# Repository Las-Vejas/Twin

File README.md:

# Twin
A macropad for both your computer and Home Assistant. Controls PC as an HID device, controls Home Assistant via ESPHome. 

I built this because I wanted a central place to control both my home/room, and my computer at the same time.
This device switches between the Home Assistant mode and PC mode with a click of a button and you receive all the feedback through the 25 leds on board.

This macropad contains:
- 14 underglow leds
- 11 switches (with leds underneath)
- RP2040
- ESP32-C6
- 1 rotary encoder

## Images

### Schematic

### PCB

## BOM

|Id |Footprint                                              |Designation                |LCSC     |Amount|Price    |Link                                                                                                                                                                                                                                                                                                                                                                                                                                                                                                                                                                                                                                                                 |
|---|-------------------------------------------------------|---------------------------|---------|------|---------|---------------------------------------------------------------------------------------------------------------------------------------------------------------------------------------------------------------------------------------------------------------------------------------------------------------------------------------------------------------------------------------------------------------------------------------------------------------------------------------------------------------------------------------------------------------------------------------------------------------------------------------------------------------------|
|1  |C_0402_1005Metric                                      |1uf                        |C14445   |100   |0.23 $US |https://www.lcsc.com/product-detail/C14445.html                                                                                                                                                                                                                                                                                                                                                                                                                                                                                                                                                                                                                      |
|2  |C_0402_1005Metric                                      |100nf                      |C60474   |100   |0.10 $US |https://www.lcsc.com/product-detail/C60474.html                                                                                                                                                                                                                                                                                                                                                                                                                                                                                                                                                                                                                      |
|3  |C_0402_1005Metric                                      |10uf                       |C315248  |20    |0.17 $US |https://www.lcsc.com/product-detail/C315248.html                                                                                                                                                                                                                                                                                                                                                                                                                                                                                                                                                                                                                     |
|4  |C_0402_1005Metric                                      |33pf                       |C107005  |100   |0.12 $US |https://www.lcsc.com/product-detail/C107005.html                                                                                                                                                                                                                                                                                                                                                                                                                                                                                                                                                                                                                     |
|7  |LED_WS2812B-2020_PLCC4_2.0x2.0mm                       |WS2812B-2020               |C965555  |40    |3.59 $US |https://www.lcsc.com/product-detail/C965555.html                                                                                                                                                                                                                                                                                                                                                                                                                                                                                                                                                                                                                     |
|8  |D_SOD-323_HandSoldering                                |D_Small                    |C191023  |50    |0.52 $US |https://www.lcsc.com/product-detail/C191023.html                                                                                                                                                                                                                                                                                                                                                                                                                                                                                                                                                                                                                     |
|9  |MX_SK6812MINI-E                                        |LED_SK6812MINI             |C5149201 |55    |4.13 $US |https://www.lcsc.com/product-detail/C5149201.html                                                                                                                                                                                                                                                                                                                                                                                                                                                                                                                                                                                                                    |
|10 |USB_C_Receptacle_GCT_USB4105-xx-A_16P_TopMnt_Horizontal|USB_C_Receptacle_USB2.0_16P|C2765186 |20    |1.23 $US |https://www.lcsc.com/product-detail/C2765186.html                                                                                                                                                                                                                                                                                                                                                                                                                                                                                                                                                                                                                    |
|12 |C_0402_1005Metric                                      |10k                        |C60490   |100   |0.08 $US |https://www.lcsc.com/product-detail/C60490.html                                                                                                                                                                                                                                                                                                                                                                                                                                                                                                                                                                                                                      |
|13 |C_0402_1005Metric                                      |5.1k                       |C105872  |100   |0.09 $US |https://www.lcsc.com/product-detail/C105872.html                                                                                                                                                                                                                                                                                                                                                                                                                                                                                                                                                                                                                     |
|14 |C_0402_1005Metric                                      |27                         |C138021  |100   |0.08 $US |https://www.lcsc.com/product-detail/C138021.html                                                                                                                                                                                                                                                                                                                                                                                                                                                                                                                                                                                                                     |
|15 |C_0402_1005Metric                                      |1k                         |C106235  |100   |0.08 $US |https://www.lcsc.com/product-detail/C106235.html                                                                                                                                                                                                                                                                                                                                                                                                                                                                                                                                                                                                                     |
|16 |C_0402_1005Metric                                      |47                         |C137973  |100   |0.09 $US |https://www.lcsc.com/product-detail/C137973.html                                                                                                                                                                                                                                                                                                                                                                                                                                                                                                                                                                                                                     |
|17 |SW_Push_SPST_NO_Alps_SKRK                              |SW_Push                    |C115357  |10    |1.31 $US |https://www.lcsc.com/product-detail/C115357.html                                                                                                                                                                                                                                                                                                                                                                                                                                                                                                                                                                                                                     |
|18 |RotaryEncoder_Alps_EC11E-Switch_Vertical_H20mm         |RotaryEncoder_Switch       |C470742  |5     |9.36 $US |https://www.lcsc.com/product-detail/C470742.html                                                                                                                                                                                                                                                                                                                                                                                                                                                                                                                                                                                                                     |
|19 |Choc_V1V2_1.00u                                        |Choc                       |         |20    |13.22 $US|https://fr.aliexpress.com/item/1005008651091078.html?spm=a2g0o.productlist.main.4.700d4fcbBPonj4&algo_pvid=be3ccfad-3712-46f3-9d73-c757c8aa3e61&algo_exp_id=be3ccfad-3712-46f3-9d73-c757c8aa3e61-3&pdp_ext_f=%7B%22order%22%3A%22447%22%2C%22eval%22%3A%221%22%2C%22fromPage%22%3A%22search%22%7D&pdp_npi=6%40dis%21EUR%216.61%215.24%21%21%2151.22%2140.63%21%40214100f417755480393871686e909e%2112000046099032296%21sea%21LU%212630435768%21X%211%210%21n_tag%3A-29919%3Bd%3Af72fadc9%3Bm03_new_user%3A-29895%3BpisId%3A5000000202142352&curPageLogUid=yKcuHdsHmziV&utparam-url=scene%3Asearch%7Cquery_from%3A%7Cx_object_id%3A1005008651091078%7C_p_origin_prod%3A|
|21 |SOT-23                                                 |MCP1700x-300xxTT           |C39051   |5     |1.88 $US |https://www.lcsc.com/product-detail/C39051.html                                                                                                                                                                                                                                                                                                                                                                                                                                                                                                                                                                                                                      |
|22 |ESP32-C6-MINI-1                                        |ESP32-C6-MINI-1            |C5736265 |5     |11.97 $US|https://www.lcsc.com/product-detail/C5736265.html                                                                                                                                                                                                                                                                                                                                                                                                                                                                                                                                                                                                                    |
|23 |QFN-56-1EP_7x7mm_P0.4mm_EP3.2x3.2mm                    |RP2040                     |C2040    |5     |4.74 $US |https://www.lcsc.com/product-detail/C2040.html                                                                                                                                                                                                                                                                                                                                                                                                                                                                                                                                                                                                                       |
|24 |Winbond_USON-8-1EP_3x2mm_P0.5mm_EP0.2x1.6mm            |W25Q16JVSS                 |C5258281 |10    |2.74 $US |https://www.lcsc.com/product-detail/C5258281.html                                                                                                                                                                                                                                                                                                                                                                                                                                                                                                                                                                                                                    |
|25 |Crystal_SMD_3225-4Pin_3.2x2.5mm                        |12MHz                      |C20625731|5     |1.45 $US |https://www.lcsc.com/product-detail/C20625731.html                                                                                                                                                                                                                                                                                                                                                                                                                                                                                                                                                                                                                   |
|   |PCB                                                    |                           |         |5     |7.00 $US |jlcpcb.com                                                                                                                                                                                                                                                                                                                                                                                                                                                                                                                                                                                                                                                           |
|   |Stencil                                                |                           |         |1     |3.05 $US |jlcpcb.com                                                                                                                                                                                                                                                                                                                                                                                                                                                                                                                                                                                                                                                           |
|   |PCB Shipping                                           |                           |         |1     |15.00 $US|jlcpcb.com                                                                                                                                                                                                                                                                                                                                                                                                                                                                                                                                                                                                                                                           |
|   |                                                       |                           |         |      |81.90 $US|                                                                                                                                                                                                                                                                                                                                                                                                                                                                                                                                                                                                                                                                     |

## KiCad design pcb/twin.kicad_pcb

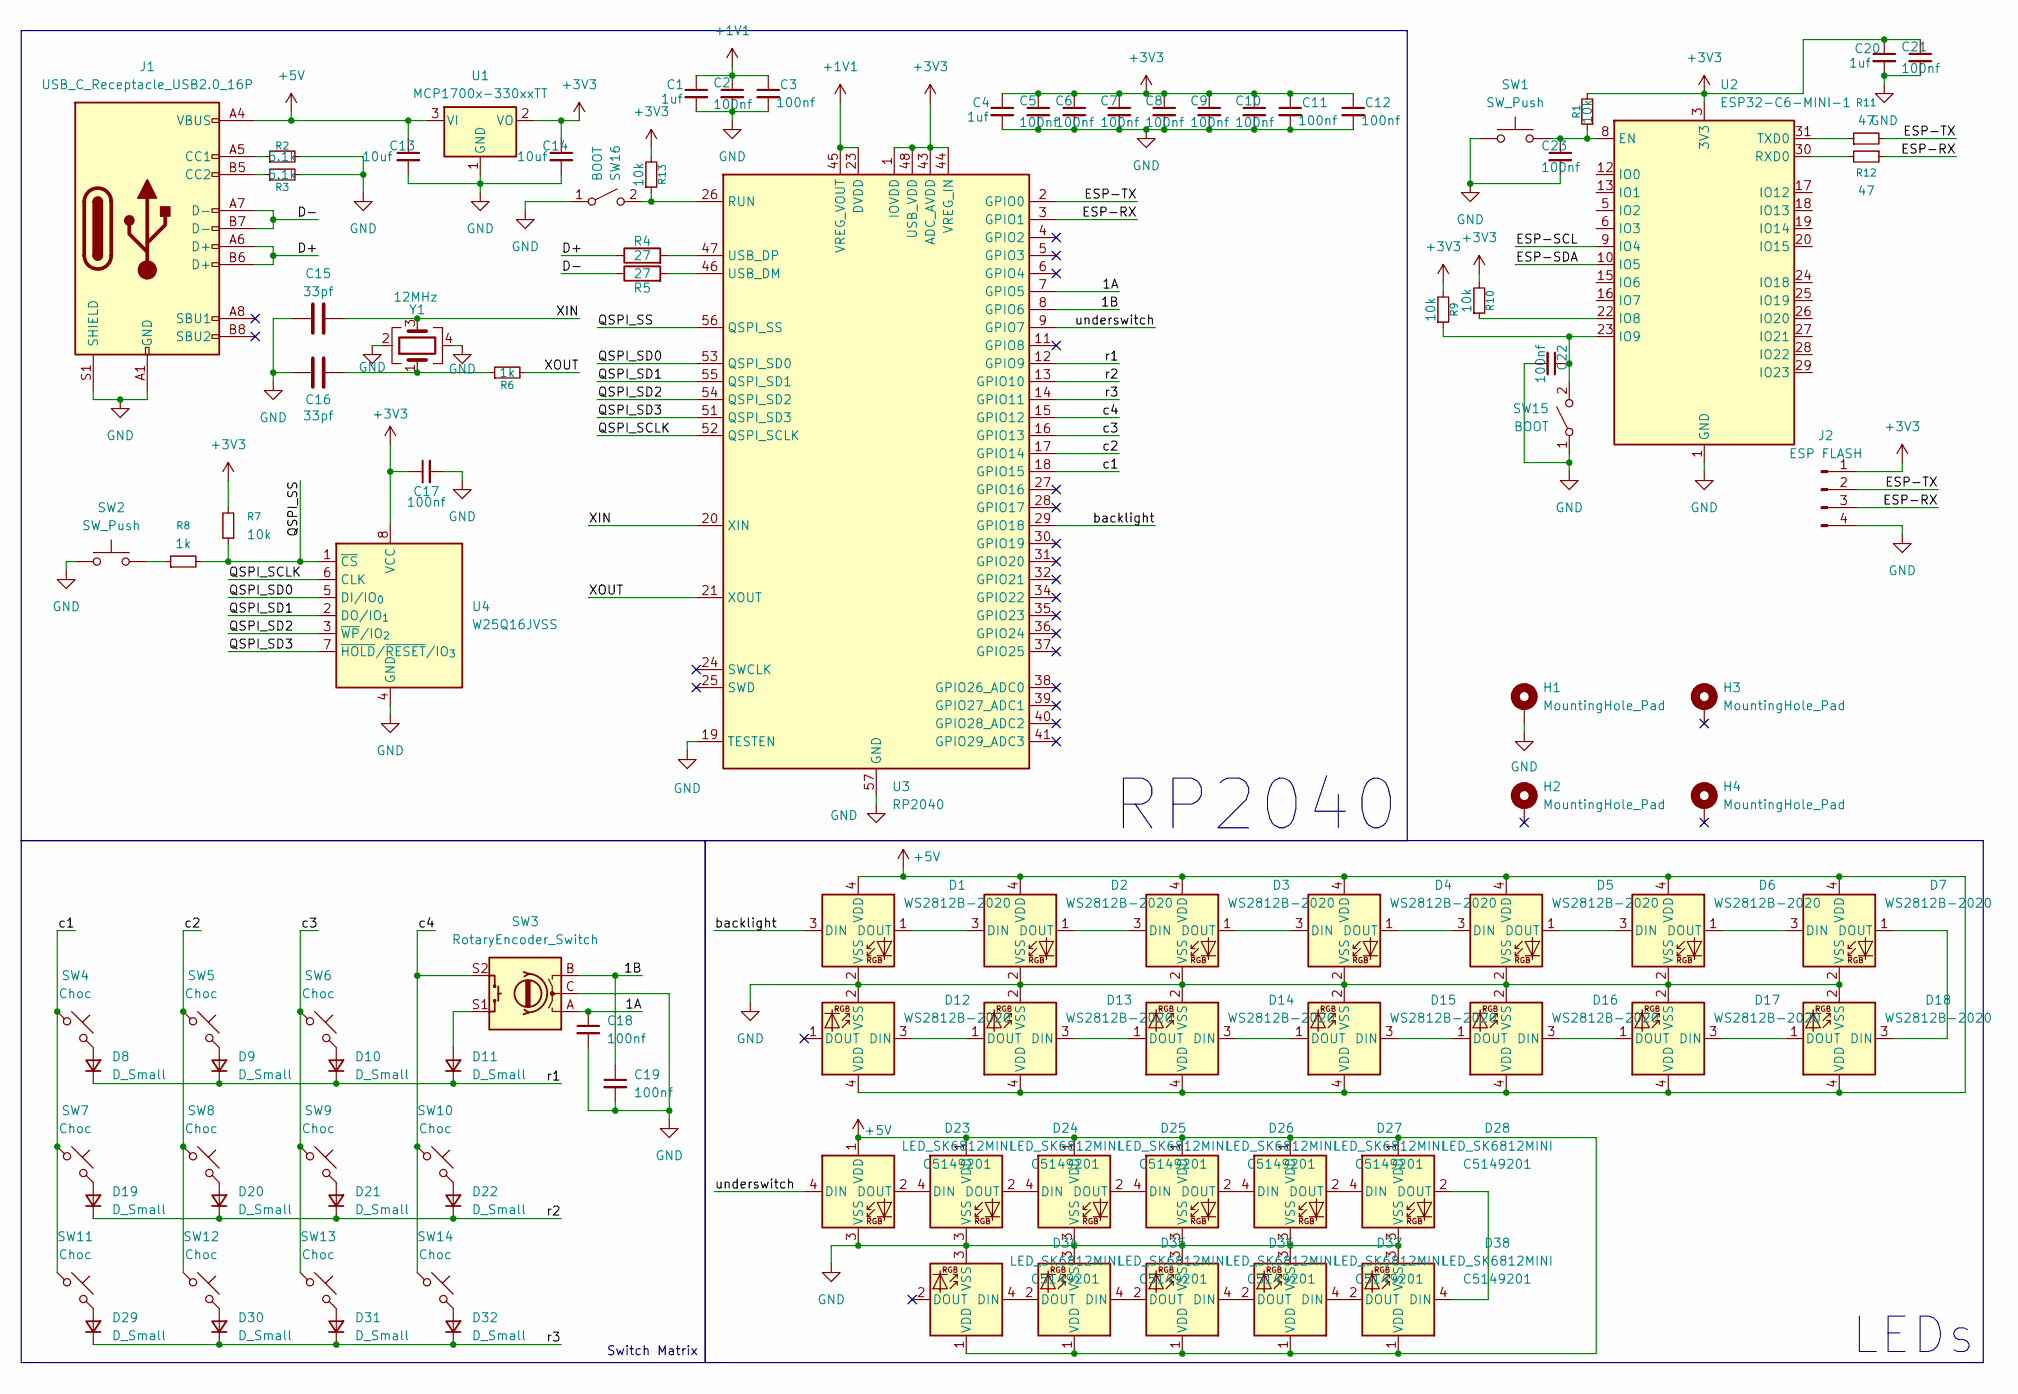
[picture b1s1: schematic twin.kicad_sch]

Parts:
C1, C4, C20: 1uf; C_0402_1005Metric
C2, C3, C5, C6, C7, C8, C9, C10, C11, C12, C17, C18, C19, C21, C22, C23: 100nf; C_0402_1005Metric
C13, C14: 10uf; C_0402_1005Metric
C15, C16: 33pf; C_0402_1005Metric
D1: WS2812B-2020; LED_WS2812B-2020_PLCC4_2.0x2.0mm; LCSC Part # C2976072
D2, D3, D4, D5, D6, D7, D12, D13, D14, D15, D16, D17, D18: WS2812B-2020; LED_WS2812B-2020_PLCC4_2.0x2.0mm
D8, D9, D10, D11, D19, D20, D21, D22, D29, D30, D31, D32: D_Small; D_SOD-323_HandSoldering
D23, D24, D25, D26, D27, D28, D34, D35, D36, D37, D38: LED_SK6812MINI; MX_SK6812MINI-E; LCSC C5149201
H1, H2, H3, H4: MountingHole_Pad; MountingHole_2.2mm_M2_DIN965_Pad
J1: USB_C_Receptacle_USB2.0_16P; USB_C_Receptacle_GCT_USB4105-xx-A_16P_TopMnt_Horizontal
J2: ESP FLASH; PinHeader_1x04_P2.54mm_Vertical
R1, R7, R9, R10, R13: 10k; C_0402_1005Metric
R2, R3: 5.1k; C_0402_1005Metric
R4, R5: 27; C_0402_1005Metric
R6, R8: 1k; C_0402_1005Metric
R11, R12: 47; C_0402_1005Metric
SW1, SW2: SW_Push; SW_Push_SPST_NO_Alps_SKRK
SW3: RotaryEncoder_Switch; RotaryEncoder_Alps_EC11E-Switch_Vertical_H20mm
SW4, SW5, SW6, SW7, SW8, SW9, SW10, SW11, SW12, SW13, SW14: Choc; Choc_V1V2_1.00u
SW15, SW16: BOOT; SW_Push_SPST_NO_Alps_SKRK
U1: MCP1700x-330xxTT; SOT-23
U2: ESP32-C6-MINI-1
U3: RP2040; QFN-56-1EP_7x7mm_P0.4mm_EP3.2x3.2mm
U4: W25Q16JVSS; Winbond_USON-8-1EP_3x2mm_P0.5mm_EP0.2x1.6mm
Y1: 12MHz; Crystal_SMD_3225-4Pin_3.2x2.5mm

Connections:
+1V1: C1.1, C2.1, C3.1, U3.23 (DVDD), U3.45 (VREG_VOUT), U3.50 (DVDD)
+3V3: C4.1, C5.1, C6.1, C7.1, C8.1, C9.1, C10.1, C11.1, C12.1, C14.1, C17.1, C20.1, C21.1, J2.1, R1.2, R7.2, R9.2, R10.2, R13.2, U1.2 (VO), U2.3 (3V3), U3.1 (IOVDD), U3.10 (IOVDD), U3.22 (IOVDD), U3.33 (IOVDD), U3.42 (IOVDD), U3.43 (ADC_AVDD), U3.44 (VREG_IN), U3.48 (USB_VDD), U3.49 (IOVDD), U4.8 (VCC)
+5V: C13.1, D1.4 (VDD), D2.4 (VDD), D3.4 (VDD), D4.4 (VDD), D5.4 (VDD), D6.4 (VDD), D7.4 (VDD), D12.4 (VDD), D13.4 (VDD), D14.4 (VDD), D15.4 (VDD), D16.4 (VDD), D17.4 (VDD), D18.4 (VDD), D23.1 (VDD), D24.1 (VDD), D25.1 (VDD), D26.1 (VDD), D27.1 (VDD), D28.1 (VDD), D34.1 (VDD), D35.1 (VDD), D36.1 (VDD), D37.1 (VDD), D38.1 (VDD), J1.A4 (VBUS), J1.A9 (VBUS), J1.B4 (VBUS), J1.B9 (VBUS), U1.3 (VI)
/1A: C18.1, SW3.A, U3.7 (GPIO5)
/1B: C19.1, SW3.B, U3.8 (GPIO6)
/D+: J1.A6 (D+), J1.B6 (D+), R4.1
/D-: J1.A7 (D-), J1.B7 (D-), R5.1
/ESP-RX: J2.3, R12.1, U3.3 (GPIO1)
/ESP-SCL: U2.9 (IO4)
/ESP-SDA: U2.10 (IO5)
/ESP-TX: J2.2, R11.2, U3.2 (GPIO0)
/QSPI_SCLK: U3.52 (QSPI_SCLK), U4.6 (CLK)
/QSPI_SD0: U3.53 (QSPI_SD0), U4.5 (DI/IO_{0})
/QSPI_SD1: U3.55 (QSPI_SD1), U4.2 (DO/IO_{1})
/QSPI_SD2: U3.54 (QSPI_SD2), U4.3 (~WP/IO_{2})
/QSPI_SD3: U3.51 (QSPI_SD3), U4.7 (~HOLD/~RESET/IO_{3})
/QSPI_SS: R7.1, R8.2, U3.56 (QSPI_SS), U4.1 (~CS)
/XIN: C15.2, U3.20 (XIN), Y1.3
/XOUT: R6.2, U3.21 (XOUT)
/backlight: D1.3 (DIN), U3.29 (GPIO18)
/c1: SW4.1, SW7.1, SW11.1, U3.18 (GPIO15)
/c2: SW5.1, SW8.1, SW12.1, U3.17 (GPIO14)
/c3: SW6.1, SW9.1, SW13.1, U3.16 (GPIO13)
/c4: SW3.S2, SW10.1, SW14.1, U3.15 (GPIO12)
/r1: D8.1 (K), D9.1 (K), D10.1 (K), D11.1 (K), U3.12 (GPIO9)
/r2: D19.1 (K), D20.1 (K), D21.1 (K), D22.1 (K), U3.13 (GPIO10)
/r3: D29.1 (K), D30.1 (K), D31.1 (K), D32.1 (K), U3.14 (GPIO11)
/underswitch: D23.4 (DIN), U3.9 (GPIO7)
GND: C1.2, C2.2, C3.2, C4.2, C5.2, C6.2, C7.2, C8.2, C9.2, C10.2, C11.2, C12.2, C13.2, C14.2, C15.1, C16.1, C17.2, C18.2, C19.2, C20.2, C21.2, C22.2, C23.2, D1.2 (VSS), D2.2 (VSS), D3.2 (VSS), D4.2 (VSS), D5.2 (VSS), D6.2 (VSS), D7.2 (VSS), D12.2 (VSS), D13.2 (VSS), D14.2 (VSS), D15.2 (VSS), D16.2 (VSS), D17.2 (VSS), D18.2 (VSS), D23.3 (VSS), D24.3 (VSS), D25.3 (VSS), D26.3 (VSS), D27.3 (VSS), D28.3 (VSS), D34.3 (VSS), D35.3 (VSS), D36.3 (VSS), D37.3 (VSS), D38.3 (VSS), H1.1 (1_1), J1.A1 (GND), J1.A12 (GND), J1.B1 (GND), J1.B12 (GND), J1.S1 (SHIELD), J2.4, R2.2, R3.2, SW1.1, SW2.1, SW3.C, SW15.1 (A), SW16.1 (A), U1.1 (GND), U2.1 (GND), U2.2 (GND), U2.11 (GND), U2.14 (GND), U2.36 (GND), U2.37 (GND), U2.38 (GND), U2.39 (GND), U2.40 (GND), U2.41 (GND), U2.42 (GND), U2.43 (GND), U2.44 (GND), U2.45 (GND), U2.46 (GND), U2.47 (GND), U2.48 (GND), U2.49 (GND), U2.50 (GND), U2.51 (GND), U2.52 (GND), U2.53 (GND), U3.19 (TESTEN), U3.57 (GND), U4.4 (GND), Y1.2, Y1.4
unnamed: C16.2, R6.1, Y1.1
unnamed: D1.1 (DOUT), D2.3 (DIN)
unnamed: D2.1 (DOUT), D3.3 (DIN)
unnamed: D3.1 (DOUT), D4.3 (DIN)
unnamed: D4.1 (DOUT), D5.3 (DIN)
unnamed: D5.1 (DOUT), D6.3 (DIN)
unnamed: D6.1 (DOUT), D7.3 (DIN)
unnamed: D8.2 (A), SW4.2
unnamed: D9.2 (A), SW5.2
unnamed: D10.2 (A), SW6.2
unnamed: D11.2 (A), SW3.S1
unnamed: D12.3 (DIN), D13.1 (DOUT)
unnamed: D13.3 (DIN), D14.1 (DOUT)
unnamed: D14.3 (DIN), D15.1 (DOUT)
unnamed: D15.3 (DIN), D16.1 (DOUT)
unnamed: D16.3 (DIN), D17.1 (DOUT)
unnamed: D17.3 (DIN), D18.1 (DOUT)
unnamed: D7.1 (DOUT), D18.3 (DIN)
unnamed: D19.2 (A), SW7.2
unnamed: D20.2 (A), SW8.2
unnamed: D21.2 (A), SW9.2
unnamed: D22.2 (A), SW10.2
unnamed: D23.2 (DOUT), D24.4 (DIN)
unnamed: D24.2 (DOUT), D25.4 (DIN)
unnamed: D25.2 (DOUT), D26.4 (DIN)
unnamed: D26.2 (DOUT), D27.4 (DIN)
unnamed: D27.2 (DOUT), D28.4 (DIN)
unnamed: D28.2 (DOUT), D38.4 (DIN)
unnamed: D29.2 (A), SW11.2
unnamed: D30.2 (A), SW12.2
unnamed: D31.2 (A), SW13.2
unnamed: D32.2 (A), SW14.2
unnamed: D34.4 (DIN), D35.2 (DOUT)
unnamed: D35.4 (DIN), D36.2 (DOUT)
unnamed: D36.4 (DIN), D37.2 (DOUT)
unnamed: D37.4 (DIN), D38.2 (DOUT)
unnamed: J1.A5 (CC1), R2.1
unnamed: J1.B5 (CC2), R3.1
unnamed: R8.1, SW2.2
unnamed: C22.1, R9.1, SW15.2 (B), U2.23 (IO9)
unnamed: R13.1, SW16.2 (B), U3.26 (RUN)
unnamed: C23.1, R1.1, SW1.2, U2.8 (EN)
unnamed: R10.1, U2.22 (IO8)
unnamed: R12.2, U2.30 (RXD0)
unnamed: R11.1, U2.31 (TXD0)
unnamed: R5.2, U3.46 (USB_DM)
unnamed: R4.2, U3.47 (USB_DP)

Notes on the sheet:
Switch Matrix
RP2040
LEDs

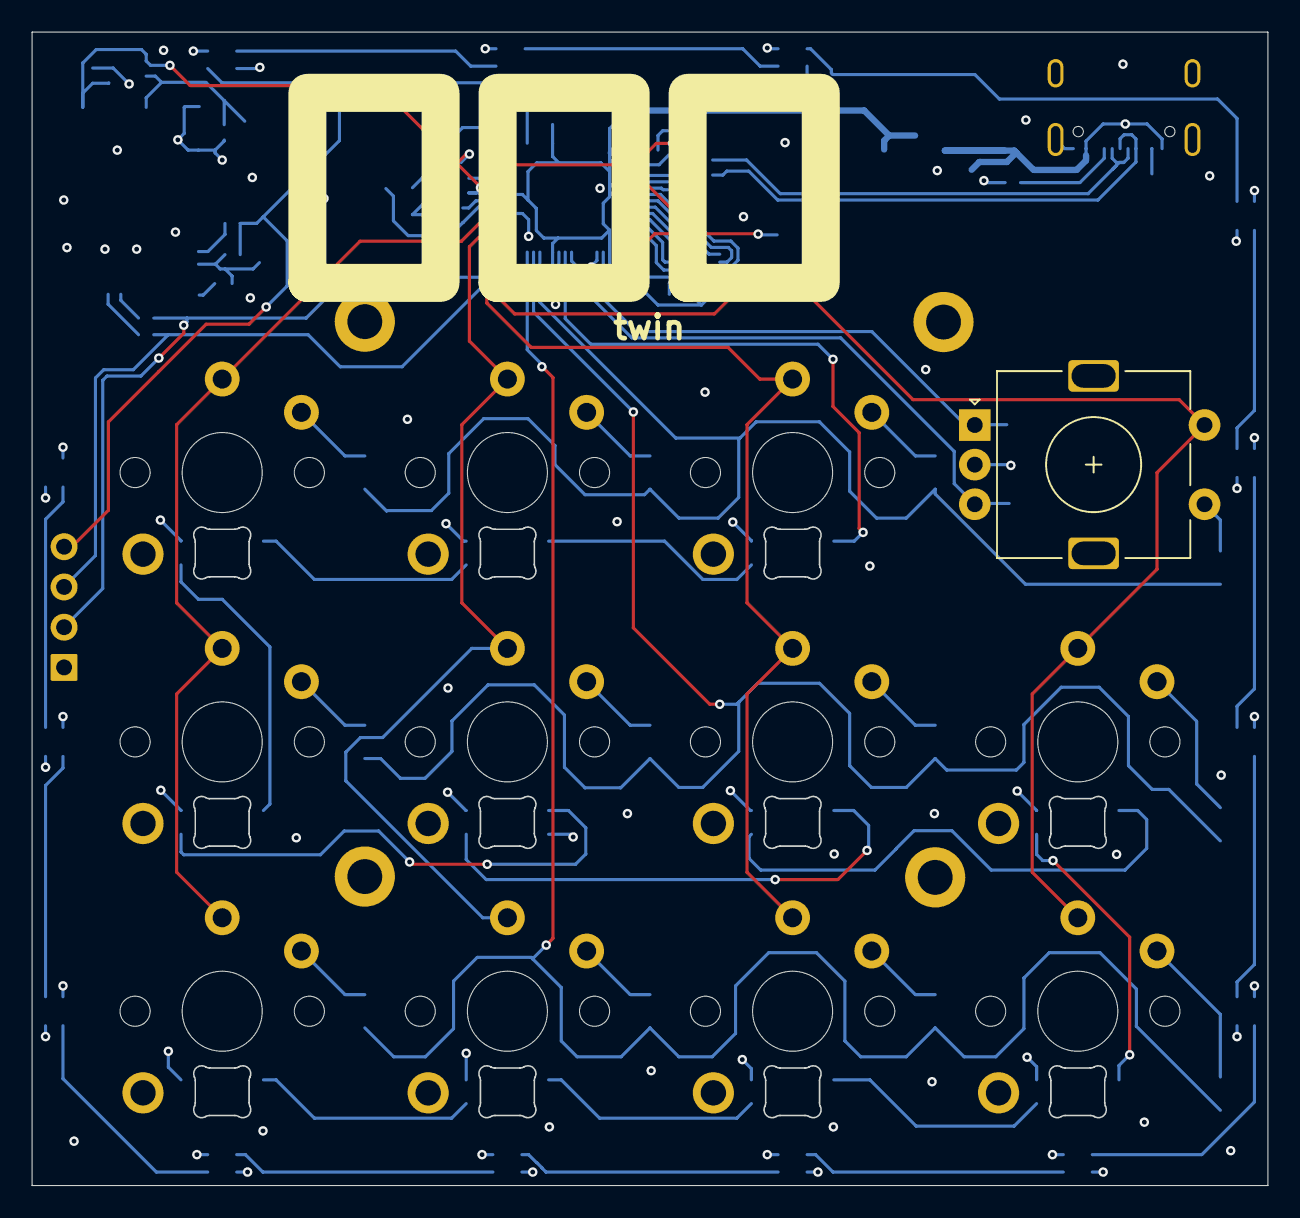
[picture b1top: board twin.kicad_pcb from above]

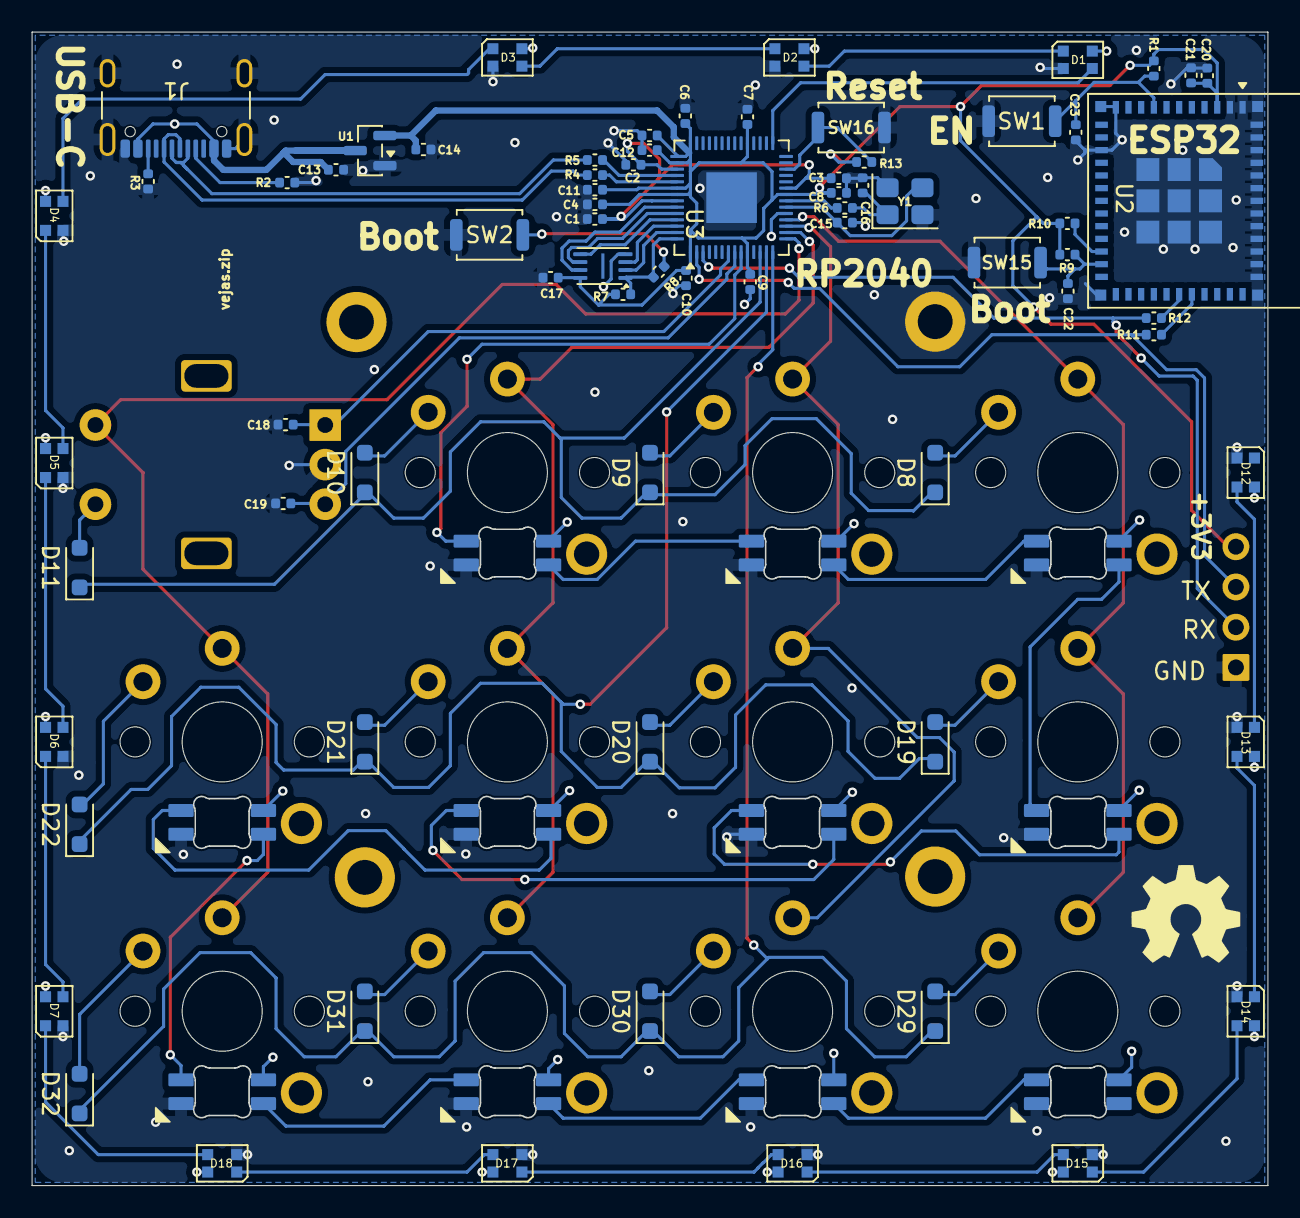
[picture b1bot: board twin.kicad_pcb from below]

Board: 4 copper layers, 78.0 x 72.8 mm, 100 parts (73 on the bottom side), 74 nets.

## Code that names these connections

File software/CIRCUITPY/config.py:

import board

# Key Matrix - match your schematic labels
ROW_PINS = [board.GPIO9, board.GPIO10, board.GPIO11]   # r1, r2, r3
COL_PINS = [board.GPIO15, board.GPIO14, board.GPIO13]  # c1, c2, c3 (+ c4 if needed)

# Rotary Encoder (top-right key position)
ENCODER_A = board.GPIO6   # 1A
ENCODER_B = board.GPIO7   # 1B
ENCODER_SW = board.GPIO8  # underswitch for encoder

# LEDs
UNDERSWITCH_LED_PIN = board.GPIO28  # underswitch (11x SK6812MINI)
UNDERGLOW_LED_PIN   = board.GPIO16  # backlight (14x WS2812B)

NUM_UNDERSWITCH = 11
NUM_UNDERGLOW   = 14

# UART to ESP32
UART_TX = board.GPIO0  # ESP-TX on schematic
UART_RX = board.GPIO1  # ESP-RX on schematic
UART_BAUD = 115200

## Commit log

2026-01-28 pcb files
2026-01-31 update pcb
2026-02-19 idek anymore i think more pcb stuff
2026-02-22 Update PCB footprints and backups
    Clean up PCB repository and update the board file. Removed macOS .DS_Store and a stale KiCad schematic lock, rotated twin-backups (deleted older backup zips and added new ones). Large edits to pcb/tw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
2026-04-07 loads of stuff
2026-04-07 Enhance README with details, images, and BOM
    Updated the README to include additional details about the macropad's functionality and added images for schematic and PCB. Also included a BOM with component details and links.
